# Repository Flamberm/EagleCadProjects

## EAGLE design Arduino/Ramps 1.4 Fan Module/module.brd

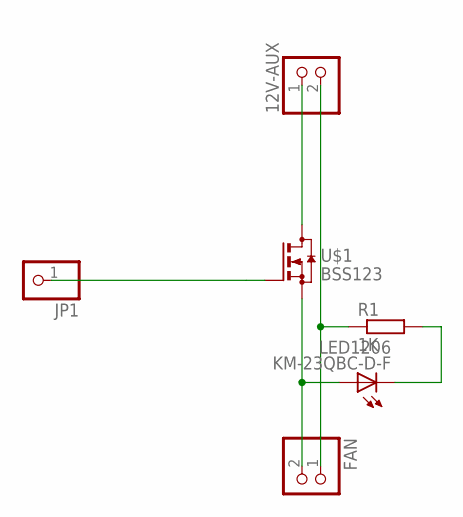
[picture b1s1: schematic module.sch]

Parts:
12V-AUX: PINHD-1X2; 1X02
FAN: PINHD-1X2; 1X02
JP1: PINHD-1X1; 1X01
KM-23QBC-D-F: LED1206
R1: 1K; R1206
U$1: BSS123; SOT23

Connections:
unnamed: JP1.1, U$1.1 (G)
unnamed: FAN.2, KM-23QBC-D-F.A, U$1.2 (S)
unnamed: 12V-AUX.1, U$1.3 (D)
unnamed: 12V-AUX.2, FAN.1, R1.1
unnamed: KM-23QBC-D-F.C, R1.2

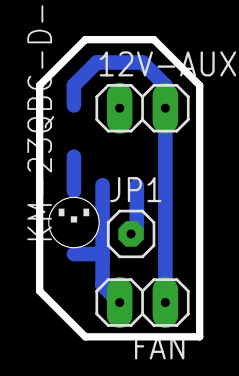
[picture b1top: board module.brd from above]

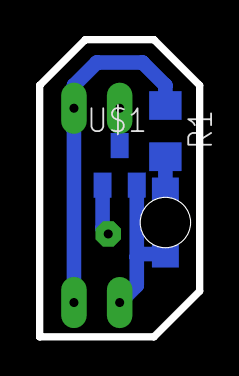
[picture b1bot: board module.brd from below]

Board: 2 copper layers, 8.9 x 16.5 mm, 6 parts (2 on the bottom side), 5 nets.

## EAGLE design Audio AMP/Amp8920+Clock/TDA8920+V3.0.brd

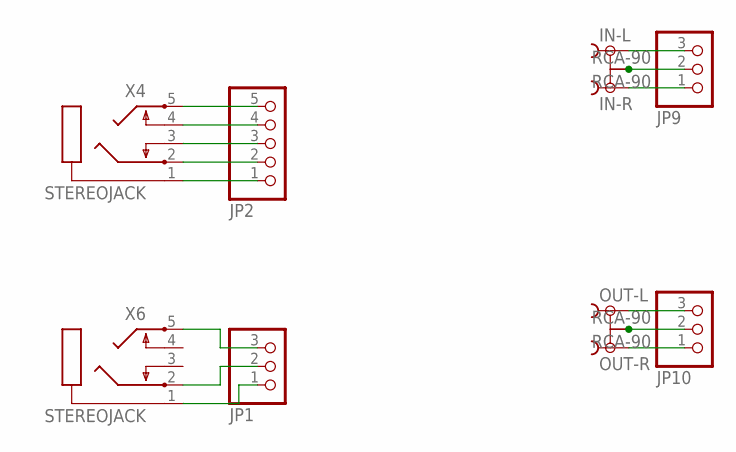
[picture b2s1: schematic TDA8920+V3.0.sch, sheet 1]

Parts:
IN-L: RCA-90
IN-R: RCA-90
JP1: PINHD-1X3/90; 1X03/90
JP2: PINHD-1X5/90; 1X05/90
JP9, JP10: PINHD-1X3; 1X03
OUT-L: RCA-90
OUT-R: RCA-90
X4, X6: STEREOJACK; STX3100

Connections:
unnamed: JP2.1, X4.1
unnamed: JP2.2, X4.2
unnamed: JP2.3, X4.3
unnamed: JP2.4, X4.4
unnamed: JP2.5, X4.5
unnamed: JP1.1, X6.1
unnamed: JP1.2, X6.2
unnamed: JP1.3, X6.5
unnamed: IN-L.1, JP9.3
unnamed: IN-R.1, JP9.1
unnamed: IN-L.2, IN-L.2@1 (2), IN-L.2@2 (2), IN-R.2, IN-R.2@1 (2), IN-R.2@2 (2), JP9.2
unnamed: JP10.2, OUT-L.2, OUT-L.2@1 (2), OUT-L.2@2 (2), OUT-R.2, OUT-R.2@1 (2), OUT-R.2@2 (2)
unnamed: JP10.1, OUT-R.1
unnamed: JP10.3, OUT-L.1

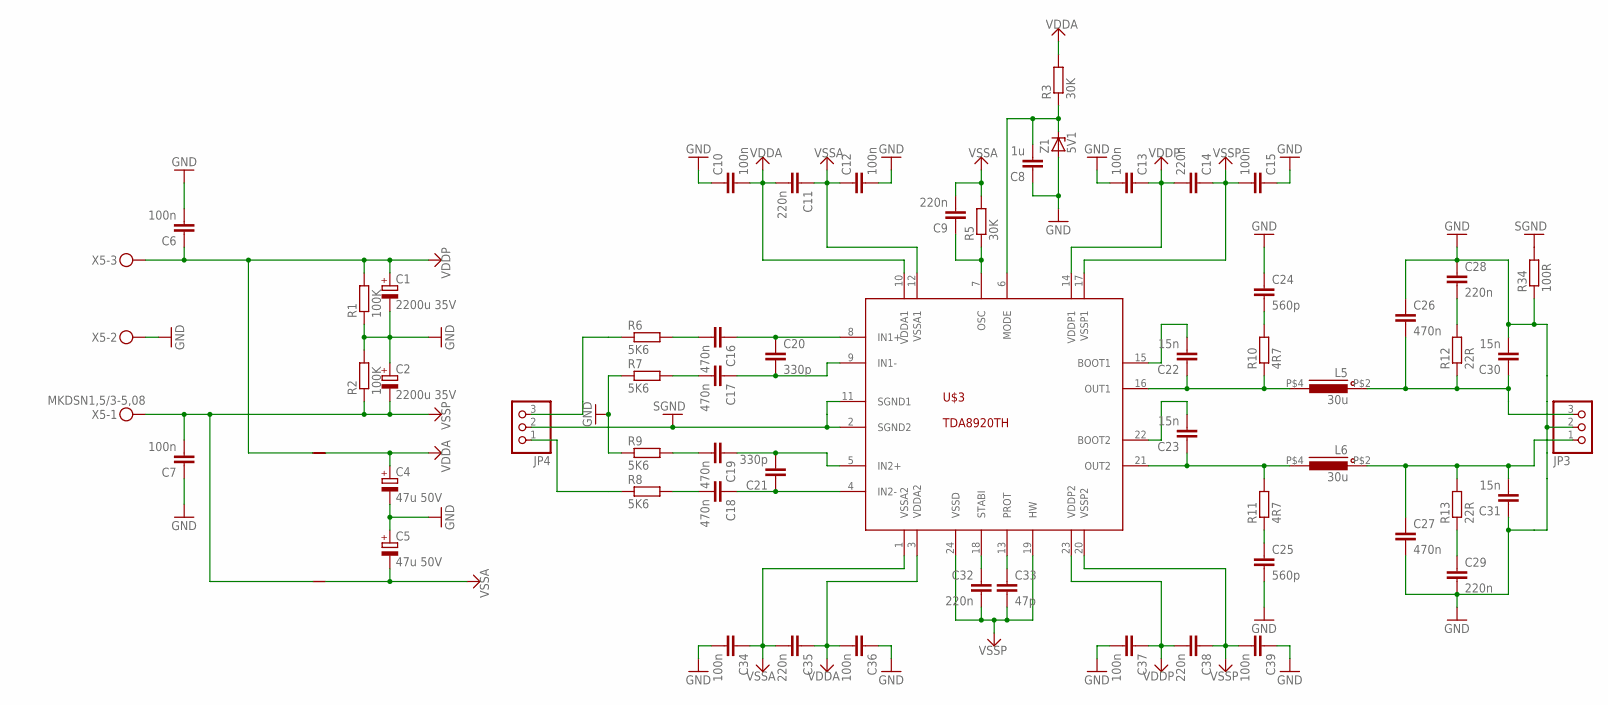
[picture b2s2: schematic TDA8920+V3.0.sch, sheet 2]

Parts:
C1, C2: 2200u 35V; E7,5-16
C4, C5: 47u 50V; E2,5-6
C6, C7, C10, C12, C13, C15, C34, C36, C37, C39: 100n; C1206
C8: 1u; C1206
C9, C11, C14, C28, C29, C32, C35, C38: 220n; C0805
C16, C17, C18, C19, C26, C27: 470n; C1206
C20, C21: 330p; C1206
C22, C23, C30, C31: 15n; C0805
C24, C25: 560p; C0805
C33: 47p; C0805
JP3, JP4: PINHD-1X3; 1X03
L5, L6: 30u; INDUCTOR_25-25
R1, R2: 100K; R1206
R3, R5: 30K; R0805
R6, R7, R8, R9: 5K6; R0805
R10, R11: 4R7; R1206
R12, R13: 22R; R2512
R34: 100R; R1206
U$1, U$2: SHORT
U$3: TDA8920THCLEAR; HSOP24
X5: MKDSN1,5/3-5,08
Z1: 5V1; SOD80C

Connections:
GND: C1.-, C2.+, C4.-, C5.+, C6.2, C7.1, C8.1, C10.1, C12.2, C13.2, C15.1, C24.1, C25.2, C26.1, C27.2, C28.1, C29.2, C30.2, C31.1, C34.2, C36.1, C37.2, C39.1, JP3.2, R1.1, R2.2, R7.1, R9.1, R34.1, X5.2, Z1.A
unnamed: C18.2, R8.2
unnamed: C18.1, C21.1, U$3.4 (IN2-)
unnamed: C19.2, R9.2
unnamed: C19.1, C21.2, U$3.5 (IN2+)
unnamed: C16.2, R6.2
unnamed: C16.1, C20.1, U$3.8 (IN1+)
unnamed: C17.2, R7.2
unnamed: C17.1, C20.2, U$3.9 (IN1-)
unnamed: C22.2, U$3.15 (BOOT1)
unnamed: C32.1, U$3.18 (STABI)
unnamed: C33.1, U$3.13 (PROT)
unnamed: C23.2, U$3.22 (BOOT2)
unnamed: C9.1, R5.1, U$3.7 (OSC)
unnamed: C23.1, L6.P$4 (2), R11.2, U$3.21 (OUT2)
unnamed: C22.1, L5.P$4 (2), R10.1, U$3.16 (OUT1)
unnamed: C25.1, R11.1
unnamed: C24.2, R10.2
unnamed: C28.2, R12.2
unnamed: C27.1, C31.2, JP3.1, L6.P$2 (1), R13.2
unnamed: C29.1, R13.1
unnamed: C8.2, R3.1, U$3.6 (MODE), Z1.C
unnamed: JP4.3, R6.1
unnamed: C26.2, C30.1, JP3.3, L5.P$2 (1), R12.1
RIGHT_AMP: JP4.1, R8.1
SGND: JP4.2, R34.2, U$3.2 (SGND2), U$3.11 (SGND1)
VDDA: C4.+, C10.2, C11.2, C35.1, C36.2, R3.2, U$2.P$2 (2), U$3.3 (VDDA2), U$3.10 (VDDA1)
VDDP: C1.+, C6.1, C13.1, C14.2, C37.1, C38.2, R1.2, U$2.P$1 (1), U$3.14 (VDDP1), U$3.23 (VDDP2), X5.3
VSSA: C5.-, C9.2, C11.1, C12.1, C34.1, C35.2, R5.2, U$1.P$2 (2), U$3.1 (VSSA2), U$3.12 (VSSA1)
VSSP: C2.-, C7.2, C14.1, C15.2, C32.2, C33.2, C38.1, C39.2, R2.1, U$1.P$1 (1), U$3.17 (VSSP1), U$3.19 (HW), U$3.20 (VSSP2), U$3.24 (VSSD), X5.1

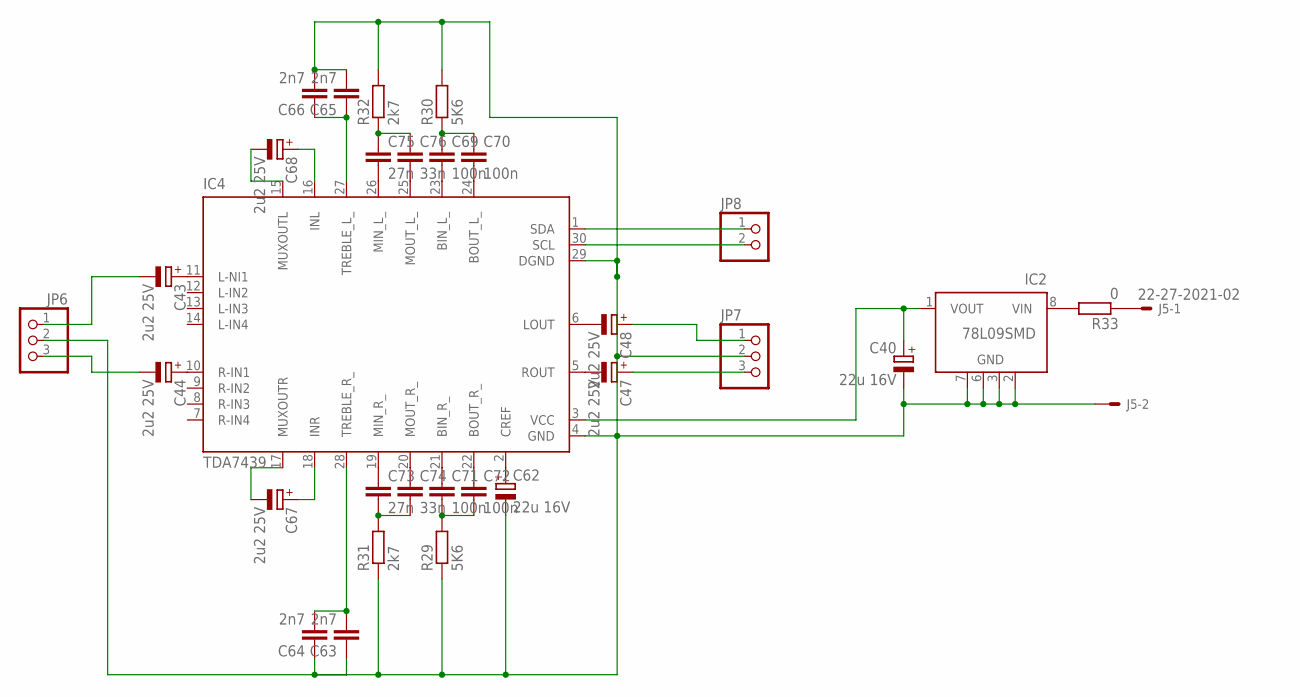
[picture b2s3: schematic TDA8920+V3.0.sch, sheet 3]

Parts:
C40, C62: 22u 16V; SMC_B
C43, C44, C47, C48, C67, C68: 2u2 25V; SMC_A
C63, C64, C65, C66: 2n7; C0805
C69, C70, C71, C72: 100n; C0805
C73, C75: 27n; C0805
C74, C76: 33n; C0805
IC2: 78L09SMD; SO08
IC4: TDA7439; SDIP30
J5: 22-27-2021-02; 6410-02
JP6, JP7: PINHD-1X3; 1X03
JP8: PINHD-1X2; 1X02
R29, R30: 5K6; R0805
R31, R32: 2k7; R1206
R33: 0; R1206

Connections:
CREF: C62.+, IC4.2 (CREF)
unnamed: C43.+, IC4.11 (L-NI1)
unnamed: C44.+, IC4.10 (R-IN1)
unnamed: C43.-, JP6.1
unnamed: C44.-, JP6.3
unnamed: C48.+, JP7.1
unnamed: C47.+, JP7.3
unnamed: C48.-, IC4.6 (LOUT)
unnamed: C47.-, IC4.5 (ROUT)
unnamed: IC4.30 (SCL), JP8.2
unnamed: IC4.1 (SDA), JP8.1
unnamed: C40.+, IC2.1 (VOUT), IC4.3 (VCC)
unnamed: IC2.8 (VIN), R33.2
unnamed: J5.1, R33.1
unnamed: C65.1, C66.1, IC4.27 (TREBLE_L_)
unnamed: C63.2, C64.2, IC4.28 (TREBLE_R_)
unnamed: C68.+, IC4.16 (INL)
unnamed: C68.-, IC4.15 (MUXOUTL)
unnamed: C67.+, IC4.18 (INR)
unnamed: C67.-, IC4.17 (MUXOUTR)
unnamed: C69.2, IC4.23 (BIN_L_)
unnamed: C70.2, IC4.24 (BOUT_L_)
unnamed: C71.1, IC4.21 (BIN_R_)
unnamed: C72.1, IC4.22 (BOUT_R_)
unnamed: C71.2, C72.2, R29.2
unnamed: C69.1, C70.1, R30.1
unnamed: C73.1, IC4.19 (MIN_R_)
unnamed: C74.1, IC4.20 (MOUT_R_)
unnamed: C75.2, IC4.26 (MIN_L_)
unnamed: C76.2, IC4.25 (MOUT_L_)
unnamed: C73.2, C74.2, R31.2
unnamed: C75.1, C76.1, R32.1
TDA_DGND: C40.-, C62.-, C63.1, C64.1, C65.2, C66.2, IC2.2 (GND), IC2.3 (GND), IC2.6 (GND), IC2.7 (GND), IC4.4 (GND), IC4.29 (DGND), J5.2, JP6.2, JP7.2, R29.1, R30.2, R31.1, R32.2

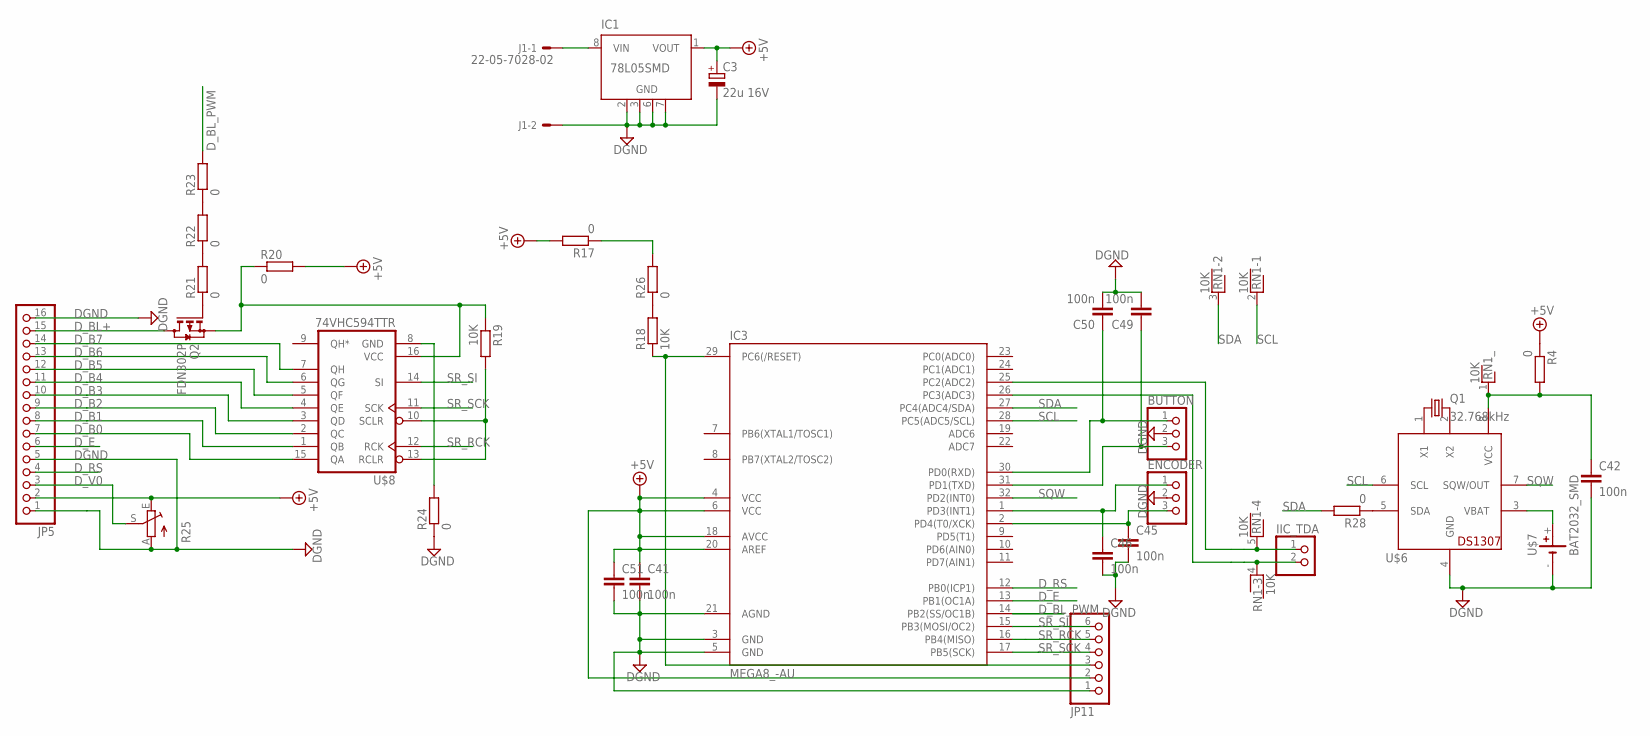
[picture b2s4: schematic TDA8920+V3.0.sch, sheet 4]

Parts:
BUTTON: PINHD-1X3; 1X03
C3: 22u 16V; SMC_B
C41, C42, C51: 100n; C0805
C45, C46, C49, C50: 100n; C1206
ENCODER: PINHD-1X3; 1X03
IC1: 78L05SMD; SO08
IC3: MEGA8_-AU; TQFP32-08
IIC_TDA: PINHD-1X2; 1X02
J1: 22-05-7028-02; 7395-02
JP5: PINHD-1X16; 1X16
JP11: PINHD-1X6; 1X06
Q1: 32.768kHz; MM20SS
Q2: FDN302P; SOT23
R4, R17, R20, R21, R22, R23, R24, R26, R28: 0; R1206
R18, R19: 10K; R1206
R25: TRIM_EU-S75H; S75H
RN1: 10K; RN-5
U$6: DS1307; SO8
U$7: BAT2032_SMD
U$8: 74VHC594TTR; TSSOP16

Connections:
+5V: C3.+, C41.1, C51.1, IC1.1 (VOUT), IC3.4 (VCC), IC3.6 (VCC), IC3.18 (AVCC), IC3.20 (AREF), JP5.2, JP11.2, R4.1, R17.2, R20.2, R25.E
DGND: BUTTON.2, C3.-, C41.2, C42.2, C45.2, C46.2, C49.2, C50.2, C51.2, ENCODER.2, IC1.2 (GND), IC1.3 (GND), IC1.6 (GND), IC1.7 (GND), IC3.3 (GND), IC3.5 (GND), IC3.21 (AGND), J1.2, JP5.1, JP5.5, JP5.16, JP11.1, R24.1, R25.A, U$6.4 (GND), U$7.-
D_B0: JP5.7, U$8.15 (QA)
D_B1: JP5.8, U$8.1 (QB)
D_B2: JP5.9, U$8.2 (QC)
D_B3: JP5.10, U$8.3 (QD)
D_B4: JP5.11, U$8.4 (QE)
D_B5: JP5.12, U$8.5 (QF)
D_B6: JP5.13, U$8.6 (QG)
D_B7: JP5.14, U$8.7 (QH)
D_BL+: JP5.15, Q2.3 (D)
D_BL_PWM: IC3.14 (PB2(SS/OC1B)), R23.2
D_E: IC3.13 (PB1(OC1A)), JP5.6
D_RS: IC3.12 (PB0(ICP1)), JP5.4
D_V0: JP5.3, R25.S
MEGA_RESET: IC3.29 (PC6(/RESET)), JP11.3, R18.1
unnamed: IC1.8 (VIN), J1.1
unnamed: Q1.4 (2), U$6.2 (X2)
unnamed: Q1.1, U$6.1 (X1)
unnamed: U$6.3 (VBAT), U$7.+
unnamed: R19.2, U$8.10 (SCLR), U$8.13 (RCLR)
unnamed: Q2.2 (S), R19.1, R20.1, U$8.16 (VCC)
unnamed: Q2.1 (G), R21.1
unnamed: R21.2, R22.1
unnamed: R22.2, R23.1
unnamed: R24.2, U$8.8 (GND)
unnamed: R18.2, R26.1
unnamed: R17.1, R26.2
unnamed: R28.1, U$6.5 (SDA)
unnamed: C42.1, R4.2, RN1.1, U$6.8 (VCC)
unnamed: C46.1, ENCODER.1, IC3.1 (PD3(INT1))
unnamed: C45.1, ENCODER.3, IC3.2 (PD4(T0/XCK))
unnamed: BUTTON.1, C50.1, IC3.30 (PD0(RXD))
unnamed: BUTTON.3, C49.1, IC3.31 (PD1(TXD))
SCL: IC3.28 (PC5(ADC5/SCL)), RN1.2, U$6.6 (SCL)
SCL_TDA: IC3.26 (PC3(ADC3)), IIC_TDA.2, RN1.4
SDA: IC3.27 (PC4(ADC4/SDA)), R28.2, RN1.3
SDA_TDA: IC3.25 (PC2(ADC2)), IIC_TDA.1, RN1.5
SQW: IC3.32 (PD2(INT0)), U$6.7 (SQW/OUT)
SR_RCK: IC3.16 (PB4(MISO)), JP11.5, U$8.12 (RCK)
SR_SCK: IC3.17 (PB5(SCK)), JP11.4, U$8.11 (SCK)
SR_SI: IC3.15 (PB3(MOSI/OC2)), JP11.6, U$8.14 (SI)

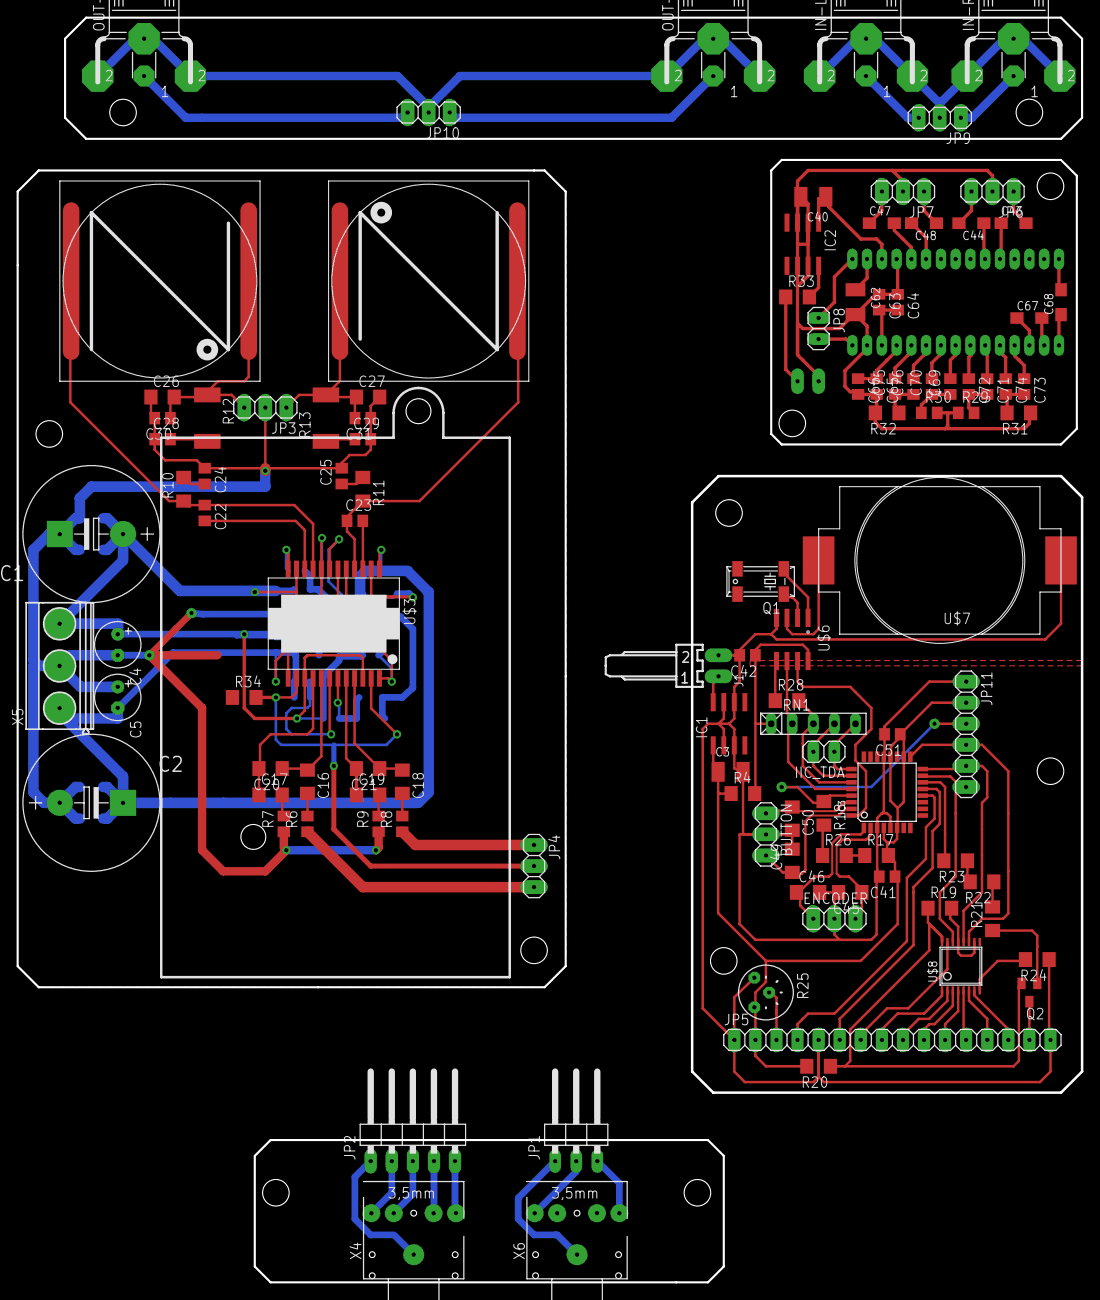
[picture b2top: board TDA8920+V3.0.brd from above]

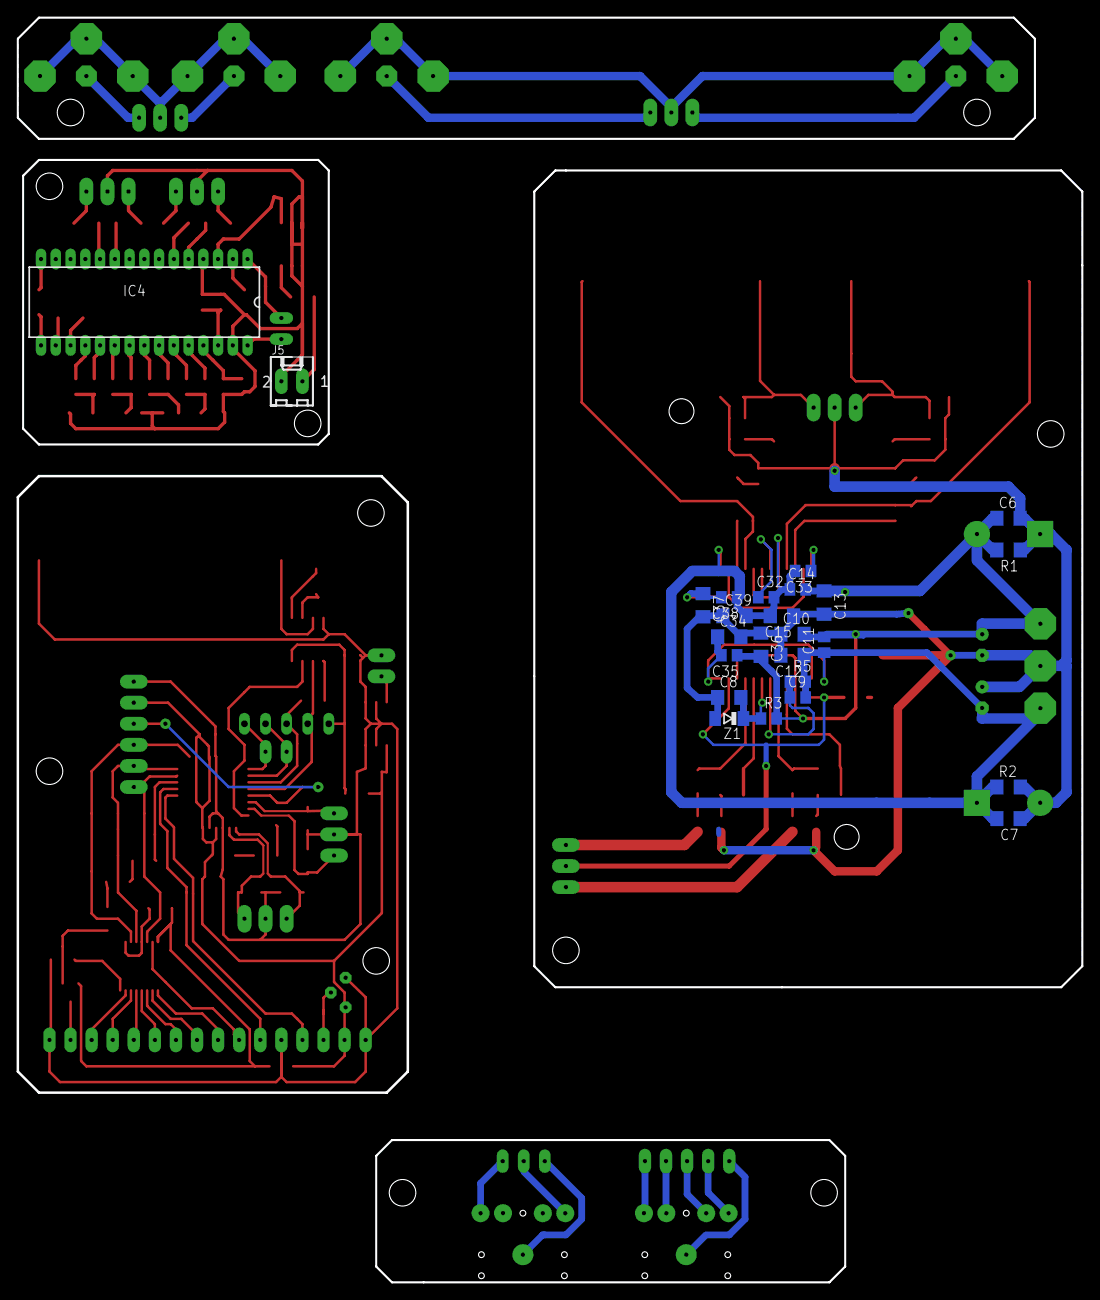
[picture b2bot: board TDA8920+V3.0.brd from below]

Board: 2 copper layers, 128.3 x 152.4 mm, 136 parts (27 on the bottom side), 119 nets.

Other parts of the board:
U$5: HEATSINK_65_42

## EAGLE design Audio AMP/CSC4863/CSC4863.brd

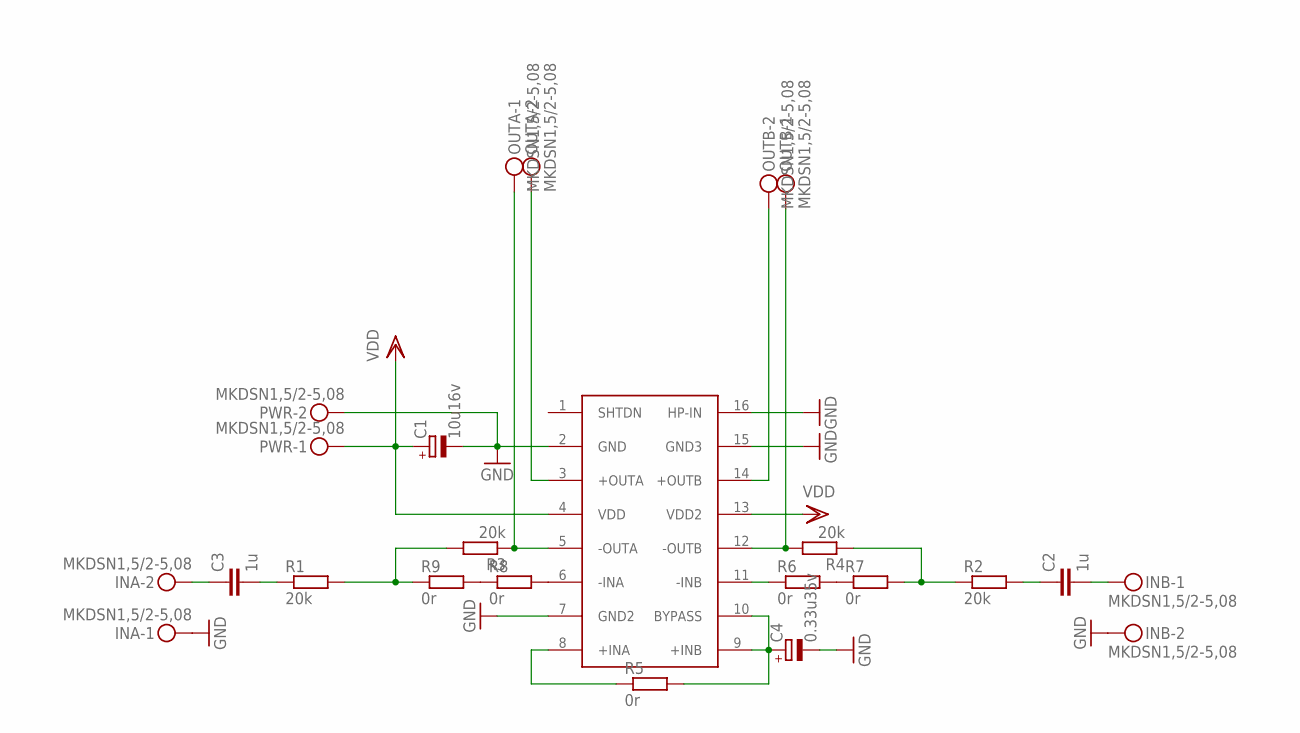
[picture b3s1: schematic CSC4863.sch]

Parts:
C1: 10u16v; SMC_A
C2, C3: 1u; C1206
C4: 0.33u35v; SMC_A
INA: MKDSN1,5/2-5,08
INB: MKDSN1,5/2-5,08
OUTA: MKDSN1,5/2-5,08
OUTB: MKDSN1,5/2-5,08
PWR: MKDSN1,5/2-5,08
R1, R2, R3, R4: 20k; R1206
R5, R6, R7, R8, R9: 0r; R1206
U$1: CSC4863; SO16

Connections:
GND: C1.-, C4.-, INA.1, INB.2, PWR.2, U$1.2 (GND), U$1.7 (GND2), U$1.15 (GND3), U$1.16 (HP-IN)
unnamed: C2.2, INB.1
unnamed: C3.1, INA.2
unnamed: C3.2, R1.1
unnamed: C2.1, R2.2
unnamed: R1.2, R3.2, R9.1
unnamed: R2.1, R4.1, R7.2
unnamed: C4.+, R5.2, U$1.9 (+INB), U$1.10 (BYPASS)
unnamed: OUTA.2, U$1.3 (+OUTA)
unnamed: OUTA.1, R3.1, U$1.5 (-OUTA)
unnamed: OUTB.2, U$1.14 (+OUTB)
unnamed: OUTB.1, R4.2, U$1.12 (-OUTB)
unnamed: R5.1, U$1.8 (+INA)
unnamed: R6.1, U$1.11 (-INB)
unnamed: R6.2, R7.1
unnamed: R8.2, U$1.6 (-INA)
unnamed: R8.1, R9.2
VDD: C1.+, PWR.1, U$1.4 (VDD), U$1.13 (VDD2)

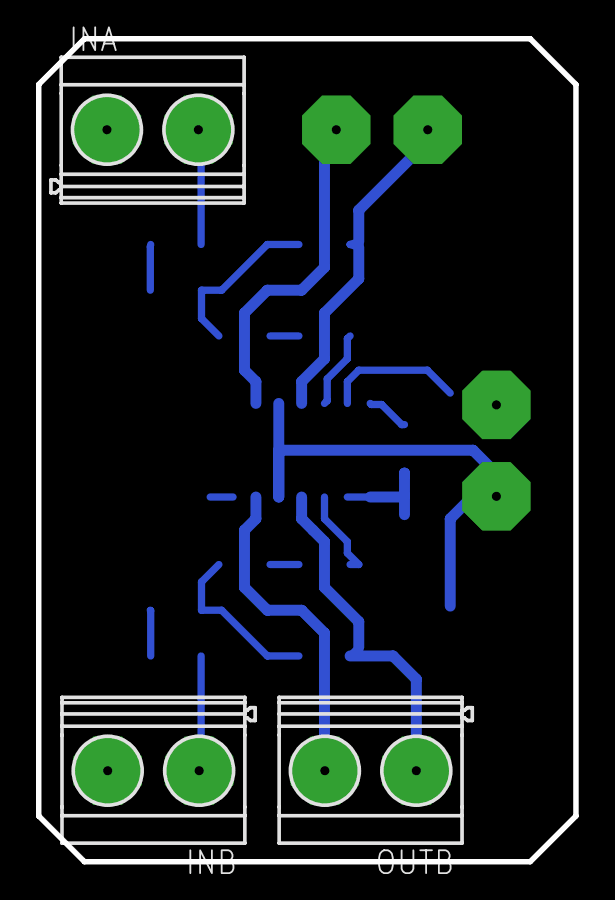
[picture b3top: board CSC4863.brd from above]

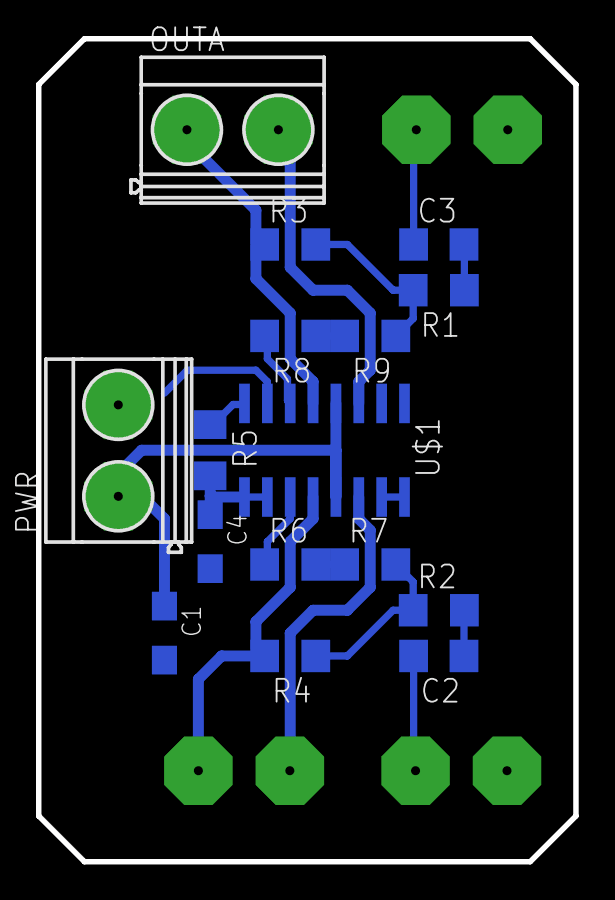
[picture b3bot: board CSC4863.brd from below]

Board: 2 copper layers, 29.8 x 45.7 mm, 19 parts (16 on the bottom side), 18 nets.

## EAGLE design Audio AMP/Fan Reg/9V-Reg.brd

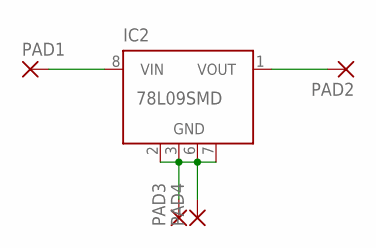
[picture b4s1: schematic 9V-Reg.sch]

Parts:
IC2: 78L09SMD; SO08
PAD1, PAD2, PAD3, PAD4: SMD2; SMD1,27-2,54

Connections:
unnamed: IC2.2 (GND), IC2.3 (GND), IC2.6 (GND), IC2.7 (GND), PAD3.1, PAD4.1
unnamed: IC2.8 (VIN), PAD1.1
unnamed: IC2.1 (VOUT), PAD2.1

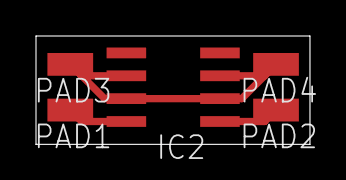
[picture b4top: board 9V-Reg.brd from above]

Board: 2 copper layers, 15.2 x 6.0 mm, 5 parts (0 on the bottom side), 3 nets.

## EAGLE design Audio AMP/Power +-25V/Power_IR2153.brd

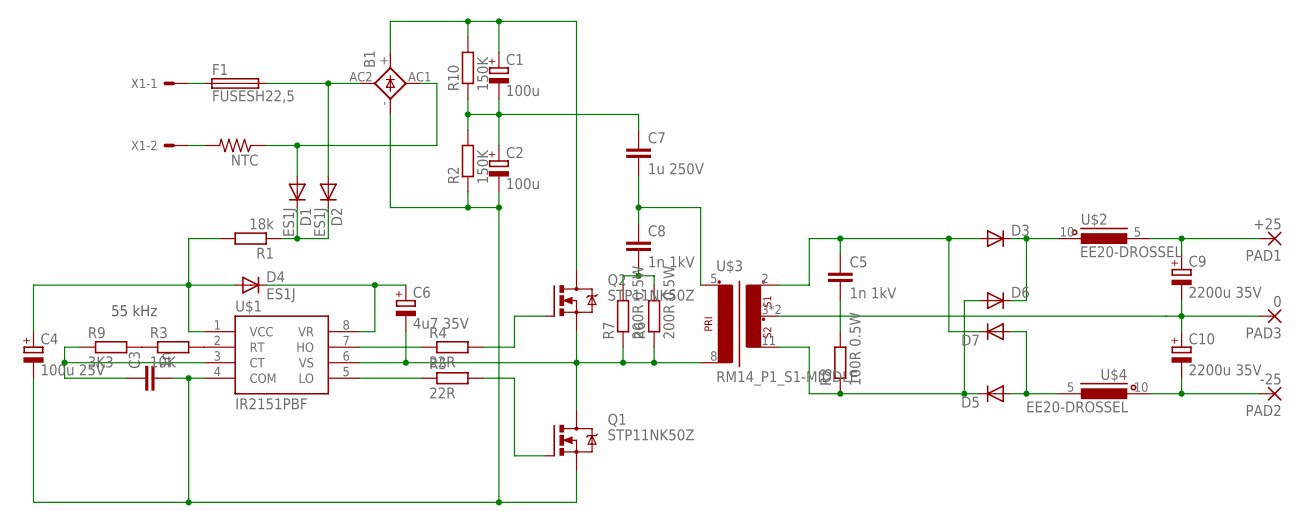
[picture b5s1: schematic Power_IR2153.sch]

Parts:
B1: KBL
C1, C2: 100u; EB22,5D
C3: 1n; C1206
C4: 100u 25V; E2,5-7
C5, C8: 1n 1kV; C050-025X075
C6: 4u7 35V; E2,5-5
C7: 1u 250V; C225-074X268
C9, C10: 2200u 35V; E7,5-16
D1, D2, D4: ES1J; DO-214AC
D3, D5, D6, D7: DIODE-SMB; SMB
F1: FUSESH22,5; SH22,5
NTC: R-US_0207/10; 0207/10
PAD1: +25; 2,54/0,8
PAD2: -25; 2,54/0,8
PAD3: 0; 2,54/0,8
Q1, Q2: STP11NK50Z; TO220BV
R1: 18k; 0922/22
R2, R10: 150K; 0207/10
R3: 10K; R1206
R4, R5: 22R; R1206
R6, R7: 200R 0.5W; 0207/10
R8: 100R 0.5W; 0207/10
R9: 3K3; R1206
U$1: IR2151PBF; DIP-8
U$2, U$4: EE20-DROSSEL; EE20_DROSSEL
U$3: RM14_P1_S1-MIDDLE; RM14
X1: KK-156-2

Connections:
COM: B1.-, C2.-, C3.2, C4.-, Q1.S, R2.1, U$1.4 (COM)
CT: C3.1, R9.1, U$1.3 (CT)
HO: R4.1, U$1.7 (HO)
LO: R5.1, U$1.5 (LO)
unnamed: NTC.2, X1.2
unnamed: F1.1, X1.1
unnamed: B1.AC1 (AC2), D1.A, NTC.1
unnamed: B1.AC2 (AC1), D2.A, F1.2
unnamed: C8.2, R6.2, R7.2
unnamed: B1.+, C1.+, Q2.D, R10.2
unnamed: C5.2, R8.2
unnamed: C7.2, C8.1, U$3.5 (P1-1)
unnamed: C1.-, C2.+, C7.1, R2.2, R10.1
unnamed: D1.C, D2.C, R1.1
unnamed: C5.1, D3.A, D7.C, U$3.2 (S1)
unnamed: D5.C, D6.A, R8.1, U$3.11 (S2)
unnamed: Q1.G, R5.2
unnamed: Q2.G, R4.2
unnamed: D5.A, D7.A, U$4.5 (2)
unnamed: D3.C, D6.C, U$2.10 (1)
unnamed: C9.-, C10.+, PAD3.1, U$3.3 (SM), U$3.10 (SM)
unnamed: C9.+, PAD1.1, U$2.5 (2)
unnamed: R3.1, R9.2
unnamed: C10.-, PAD2.1, U$4.10 (1)
RT: R3.2, U$1.2 (RT)
VCC: C4.+, D4.A, R1.2, U$1.1 (VCC)
VR: C6.+, D4.C, U$1.8 (VR)
VS: C6.-, Q1.D, Q2.S, R6.1, R7.1, U$1.6 (VS), U$3.8 (P1-2)

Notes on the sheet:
55 kHz

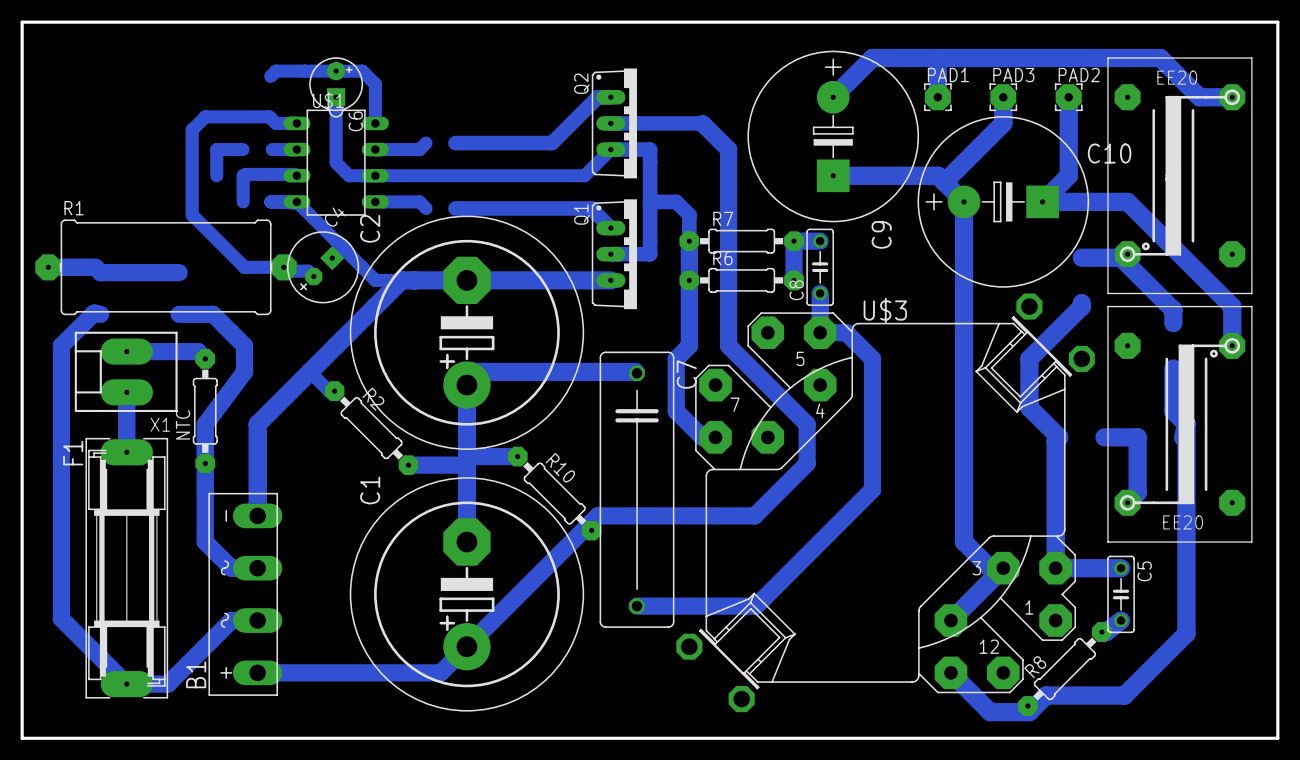
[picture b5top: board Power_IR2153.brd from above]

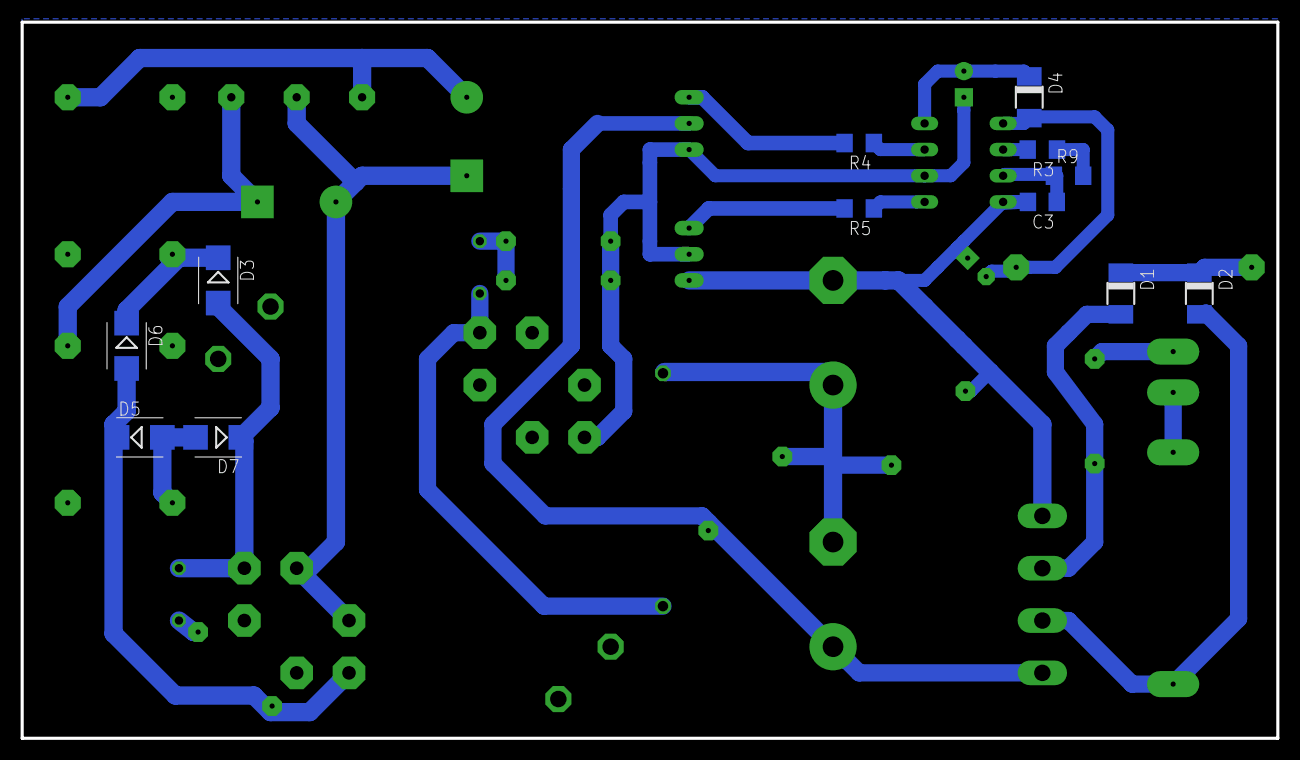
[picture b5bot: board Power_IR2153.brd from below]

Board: 2 copper layers, 121.9 x 69.5 mm, 40 parts (12 on the bottom side), 28 nets.

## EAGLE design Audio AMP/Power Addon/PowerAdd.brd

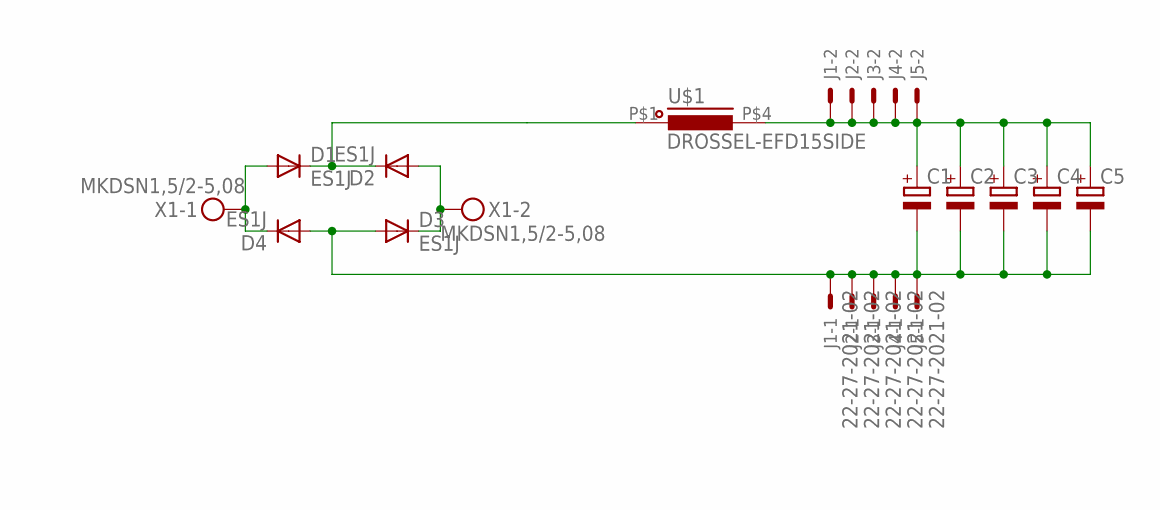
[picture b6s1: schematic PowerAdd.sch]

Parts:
C1, C2, C3, C4, C5: CPOL-EUE2.5-6; E2,5-6
D1, D2, D3, D4: ES1J; DO214AC
J1, J2, J3, J4, J5: 22-27-2021-02; 6410-02
U$1: DROSSEL-EFD15SIDE; EFD15-4PIN
X1: MKDSN1,5/2-5,08

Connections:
unnamed: C1.+, C2.+, C3.+, C4.+, C5.+, J1.2, J2.2, J3.2, J4.2, J5.2, U$1.P$4 (2)
unnamed: D1.C, D2.C, U$1.P$1 (1)
unnamed: C1.-, C2.-, C3.-, C4.-, C5.-, D3.A, D4.A, J1.1, J2.1, J3.1, J4.1, J5.1
unnamed: D2.A, D3.C, X1.2
unnamed: D1.A, D4.C, X1.1

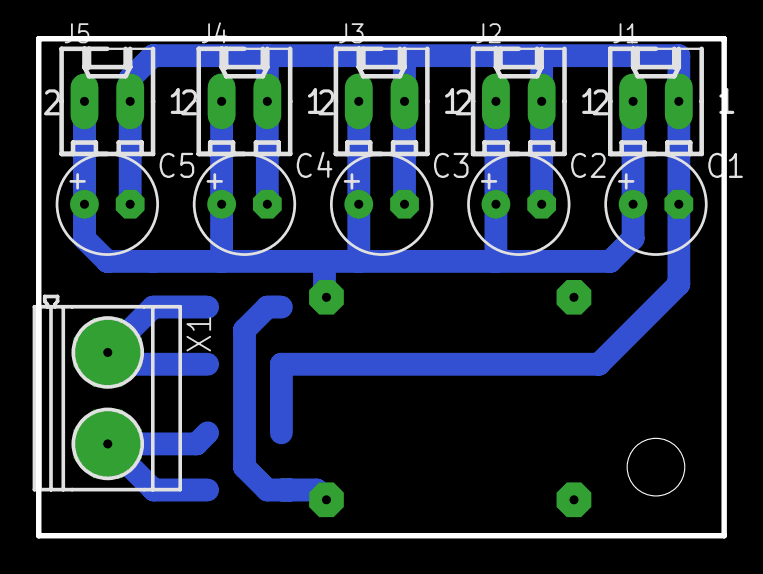
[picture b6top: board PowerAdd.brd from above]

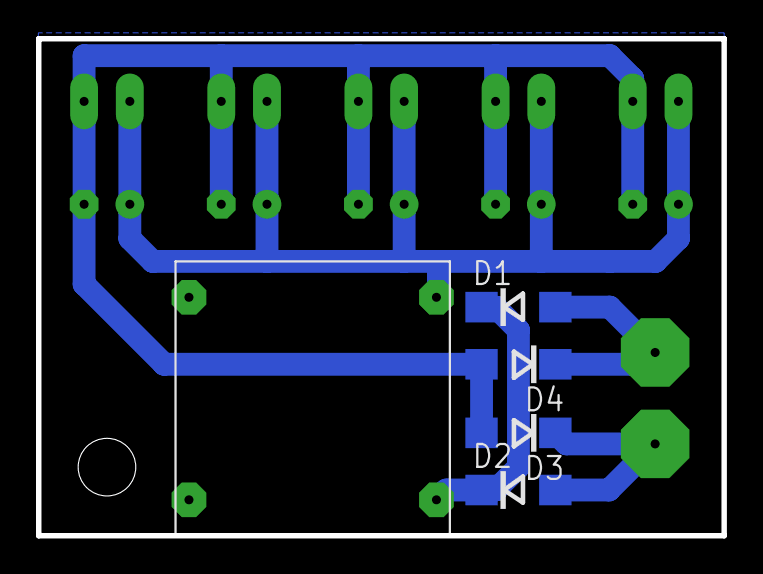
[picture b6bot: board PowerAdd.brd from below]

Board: 2 copper layers, 38.1 x 27.6 mm, 16 parts (5 on the bottom side), 5 nets.
